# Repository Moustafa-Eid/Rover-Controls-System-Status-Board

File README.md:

# Rover-Controls-System-Status-Board

**Objective:**

Create a LED status board to display if other boards on the rover are working. All devices wired to this board will be outputting either a high or low signal. The LED board will output a green light if the signal is high and a red light if the signal is low. Power for this led will NOT be coming from the signal, it will be coming straight from the lowered voltage which came from the 12V line). There are 8 signals that will be sent to this board. 

**Block Diagram:**

**My Process**
- Researched different RGB LED's and used the datasheets to calculate the maximum current consumption for 8 LED's. Factored in Size of LED and Visibility
- Researched and came up with a couple different options for the LED controller
  - First I looked in to using 2 NPN BJT's to act like a digital switch for the incoming signal. When the signal is high, the BJT is in saturation therefore it acts like a short circuit allowing the signal to pass. When the signal is Low, the BJT is in Cut-Off mode therefore it acts like a open-circuit and the LED is Off. 2 BJT's per LED would be used
    - I did not go with this design due to the extra amount of chips it would take and it would make the board a lot more complicated than needed
  - The second option I researched and ended up using is the Triple 2-channel analog demultiplexer IC. This is a chip that contains 3 1 to 2 Demultiplexers per chip. this is good as it reuces the amount of extra components and I would only need 3 IC's to cover 8 signals
    - The way it works is that it takes the signal as the selector and if the signal is low the input which is the 5V line would go to red and if the signal is high, the 5V input would go to green. Meaning that initially all LED's are red and once a signal is sent from the respective devices, the LED turns green
- Using all these components, I calculated the final total current consumption and chose an appropriate LDO to step-down the incoming 12V input to 5V which is spread out among the board. The LDO was chosen with double the current specifications to ensure safety and working operation all the time
- The signal is inputted to the 8 screw terminals on the PCB and the 12V input goes through the molex connector on the PCB.
- Made use of polygons to prevent overheating and created the bottom plane as the ground plane, therefore used polygons to bring the GND to the surface and connect to the components.
- The top plane was made as the 5V plane, therefore reducing the amount of wires on the board. 

**Final Design**

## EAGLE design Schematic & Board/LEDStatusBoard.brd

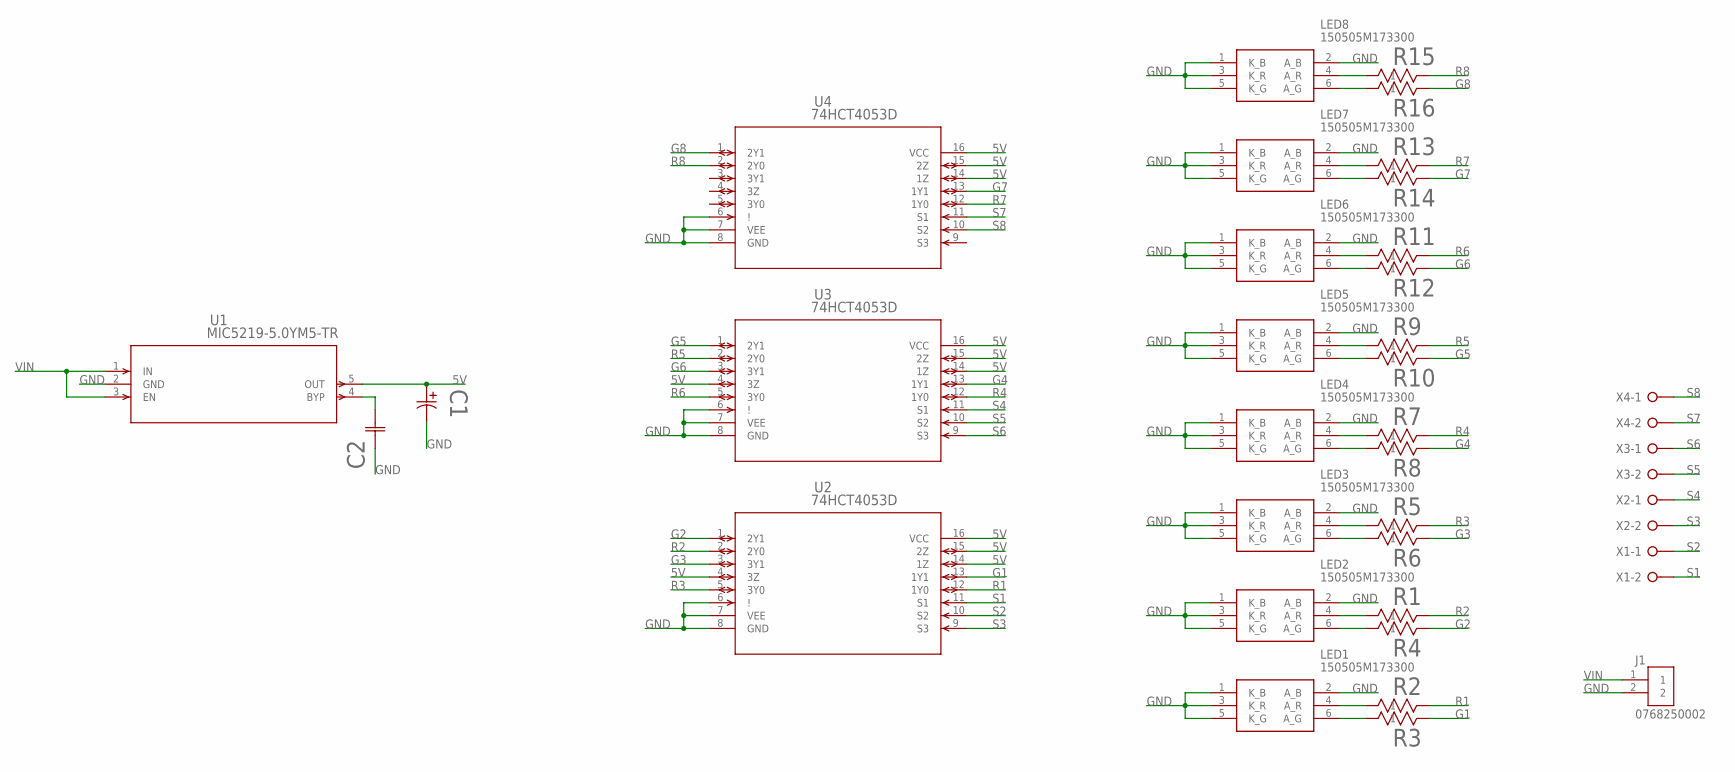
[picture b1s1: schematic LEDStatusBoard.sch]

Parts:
C1: UWX1H2R2MCL1GB; PCAP_4X5.4-ELECT_NCA
C2: 1206AA471JAT1A; CAP_1206_AVX
J1: 0768250002; MOLEX_0768250002
LED1, LED2, LED3, LED4, LED5, LED6, LED7, LED8: 150505M173300
R1, R2, R3, R4, R5, R6, R7, R8, R9, R10, R11, R12, R13, R14, R15, R16: RMCF1206JT130R; RES_RMCF1206_STP
U1: MIC5219-5.0YM5-TR; SOT-23-5_M5_MCH
U2, U3, U4: 74HCT4053D; SOT109-1_NXP
X1, X2, X3, X4: W237-02P; W237-132

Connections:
5V: C1.1, U1.5 (OUT), U2.4 (3Z), U2.14 (1Z), U2.15 (2Z), U2.16 (VCC), U3.4 (3Z), U3.14 (1Z), U3.15 (2Z), U3.16 (VCC), U4.14 (1Z), U4.15 (2Z), U4.16 (VCC)
G1: R3.2, U2.13 (1Y1)
G2: R4.2, U2.1 (2Y1)
G3: R6.2, U2.3 (3Y1)
G4: R8.2, U3.13 (1Y1)
G5: R10.2, U3.1 (2Y1)
G6: R12.2, U3.3 (3Y1)
G7: R14.2, U4.13 (1Y1)
G8: R16.2, U4.1 (2Y1)
GND: C1.2, C2.1, J1.2, LED1.1 (K_B), LED1.2 (A_B), LED1.3 (K_R), LED1.5 (K_G), LED2.1 (K_B), LED2.2 (A_B), LED2.3 (K_R), LED2.5 (K_G), LED3.1 (K_B), LED3.2 (A_B), LED3.3 (K_R), LED3.5 (K_G), LED4.1 (K_B), LED4.2 (A_B), LED4.3 (K_R), LED4.5 (K_G), LED5.1 (K_B), LED5.2 (A_B), LED5.3 (K_R), LED5.5 (K_G), LED6.1 (K_B), LED6.2 (A_B), LED6.3 (K_R), LED6.5 (K_G), LED7.1 (K_B), LED7.2 (A_B), LED7.3 (K_R), LED7.5 (K_G), LED8.1 (K_B), LED8.2 (A_B), LED8.3 (K_R), LED8.5 (K_G), U1.2 (GND), U2.6 (!), U2.7 (VEE), U2.8 (GND), U3.6 (!), U3.7 (VEE), U3.8 (GND), U4.6 (!), U4.7 (VEE), U4.8 (GND)
unnamed: C2.2, U1.4 (BYP)
unnamed: LED1.4 (A_R), R2.1
unnamed: LED1.6 (A_G), R3.1
unnamed: LED2.4 (A_R), R1.1
unnamed: LED2.6 (A_G), R4.1
unnamed: LED3.4 (A_R), R5.1
unnamed: LED3.6 (A_G), R6.1
unnamed: LED4.4 (A_R), R7.1
unnamed: LED4.6 (A_G), R8.1
unnamed: LED5.4 (A_R), R9.1
unnamed: LED5.6 (A_G), R10.1
unnamed: LED6.4 (A_R), R11.1
unnamed: LED6.6 (A_G), R12.1
unnamed: LED7.4 (A_R), R13.1
unnamed: LED7.6 (A_G), R14.1
unnamed: LED8.4 (A_R), R15.1
unnamed: LED8.6 (A_G), R16.1
R1: R2.2, U2.12 (1Y0)
R2: R1.2, U2.2 (2Y0)
R3: R5.2, U2.5 (3Y0)
R4: R7.2, U3.12 (1Y0)
R5: R9.2, U3.2 (2Y0)
R6: R11.2, U3.5 (3Y0)
R7: R13.2, U4.12 (1Y0)
R8: R15.2, U4.2 (2Y0)
S1: U2.11 (S1), X1.2
S2: U2.10 (S2), X1.1
S3: U2.9 (S3), X2.2
S4: U3.11 (S1), X2.1
S5: U3.10 (S2), X3.2
S6: U3.9 (S3), X3.1
S7: U4.11 (S1), X4.2
S8: U4.10 (S2), X4.1
VIN: J1.1, U1.1 (IN), U1.3 (EN)

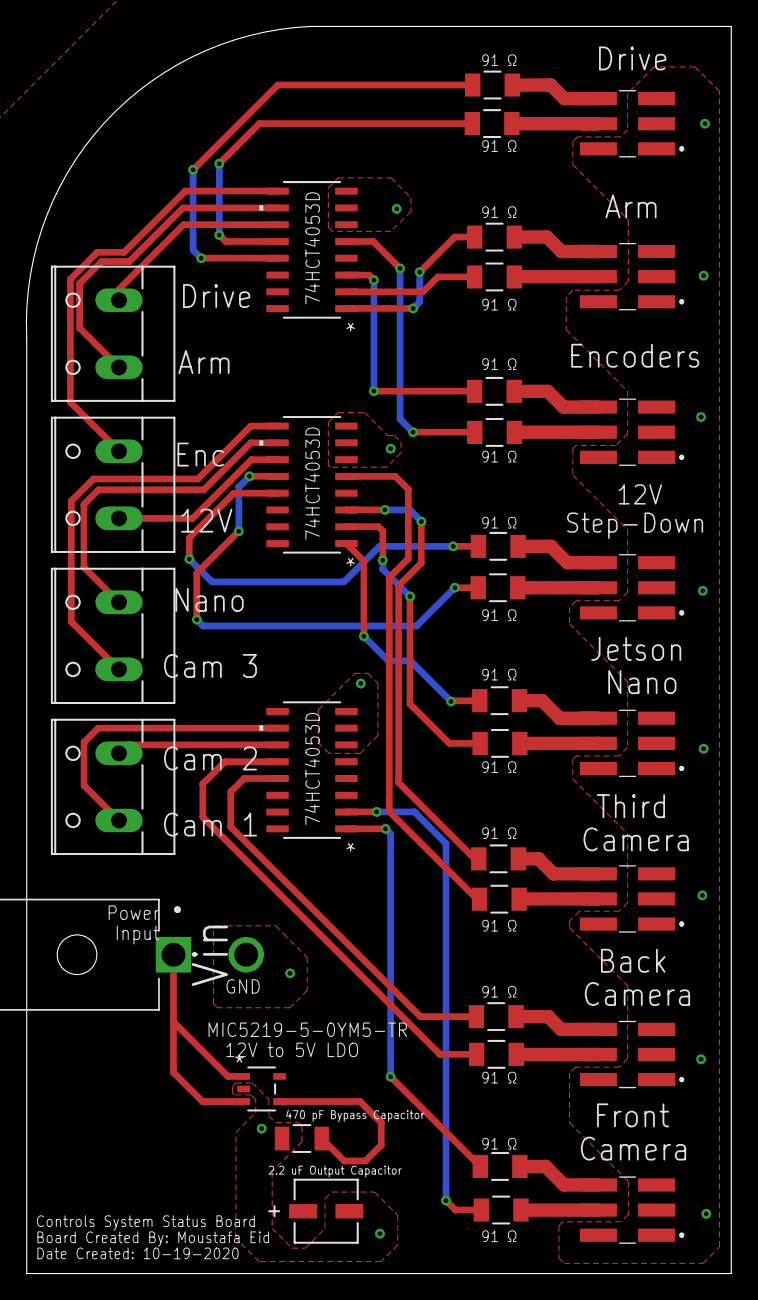
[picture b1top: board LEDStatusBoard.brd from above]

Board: 2 copper layers, 53.3 x 94.4 mm, 35 parts (0 on the bottom side), 44 nets.

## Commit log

2020-10-19 Eagle Project File - NO LABELS
2020-10-19 Images
2020-10-19 Final PCB Images
2020-10-19 Commited Rover Block Diagram
2020-10-19 Finished README of the design process
2020-10-19 Update README Images
2020-10-19 Clean up repository
2020-10-19 Updated Image Locations

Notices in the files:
parts and their libraries:
COPYRIGHT: Copyright (C) 2018 Accelerated Designs. All rights reserved
